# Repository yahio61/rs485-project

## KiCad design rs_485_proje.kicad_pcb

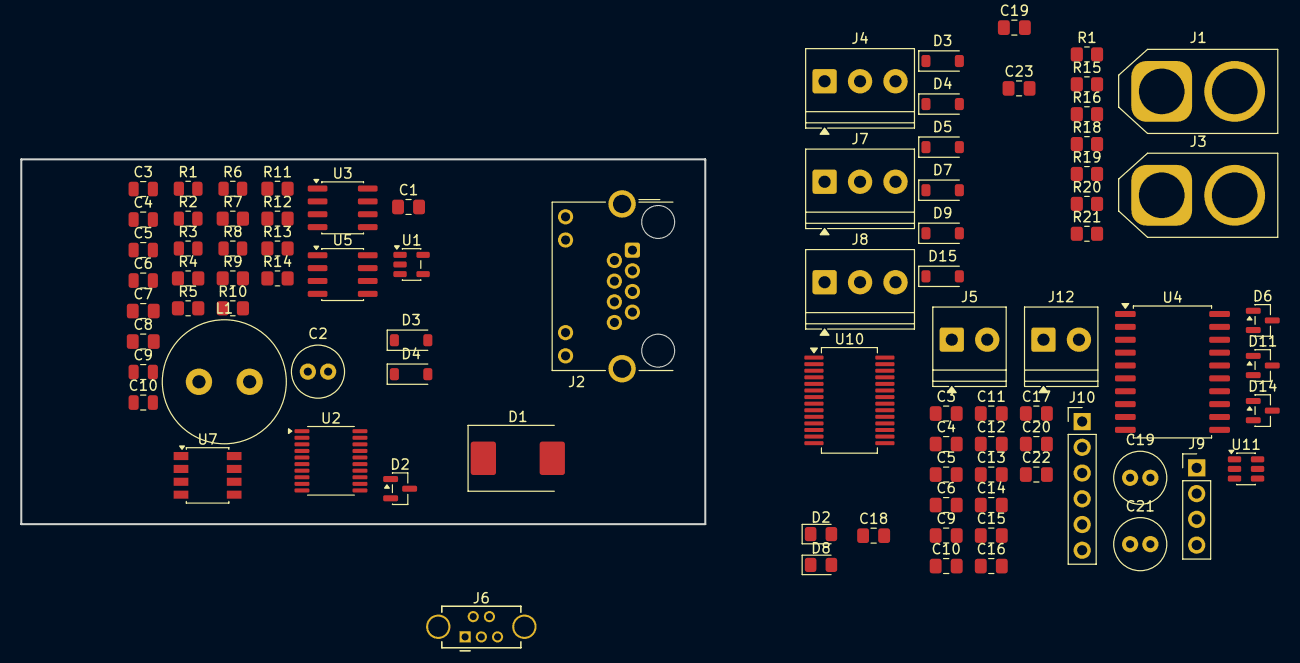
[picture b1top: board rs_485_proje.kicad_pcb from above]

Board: 2 copper layers, 67.5 x 36.0 mm, 86 parts (0 on the bottom side), 52 nets, no tracks yet.

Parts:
C1, C18: 4.7uf; C_0805_2012Metric_Pad1.18x1.45mm_HandSolder
C2: 100uf; C_Radial_D5.0mm_H11.0mm_P2.00mm
C3, C4#2, C5, C6#2: 100nf; C_0805_2012Metric
C3#2, C4, C5#2, C6, C10#2, C11, C12, C13, C14, C16: 100nF; C_0805_2012Metric_Pad1.18x1.45mm_HandSolder
C7: 1uf; C_0805_2012Metric_Pad1.18x1.45mm_HandSolder
C8: 2.2uf; C_0805_2012Metric_Pad1.18x1.45mm_HandSolder
C9, C22: 10nf; C_0805_2012Metric_Pad1.18x1.45mm_HandSolder
C9#2, C10: 4.5n; C_0805_2012Metric
C15: 100nf; C_0805_2012Metric_Pad1.18x1.45mm_HandSolder
C17, C20: 4.7nf; C_0805_2012Metric_Pad1.18x1.45mm_HandSolder
C19, C21: 10uf; C_Radial_D5.0mm_H11.0mm_P2.00mm
C19#2, C23: 10uf; C_0805_2012Metric_Pad1.18x1.45mm_HandSolder
D1: SS34; D_SMC
D2, D8: LED; LED_0805_2012Metric_Pad1.15x1.40mm_HandSolder
D2#2, D6: SM712_SOT23; SOT-23
D3, D4: 3.3V; D_SOD-123
D3#2, D4#2, D5, D7, D9, D15: 1N5819; D_SOD-123
D11, D14: BZX84Cxx; SOT-23
J1: xt60_female; AMASS_XT60-F_1x02_P7.20mm_Vertical
J2: RJ45_LED; RJ45_Connfly_DS1128-09-S8xx-S_Horizontal
J3: xt60_male; AMASS_XT60-M_1x02_P7.20mm_Vertical
J4: Led_conn; TerminalBlock_Phoenix_PT-1,5-3-3.5-H_1x03_P3.50mm_Horizontal
J5: P_E_SENSOR_1; TerminalBlock_Phoenix_PT-1,5-2-3.5-H_1x02_P3.50mm_Horizontal
J6: USB_B_Mini; USB_Mini-B_Tensility_54-00023_Vertical_CircularHoles
J7: H_E_sensor_1; TerminalBlock_Phoenix_PT-1,5-3-3.5-H_1x03_P3.50mm_Horizontal
J8: H_E_sensor_2; TerminalBlock_Phoenix_PT-1,5-3-3.5-H_1x03_P3.50mm_Horizontal
J9: Debug; PinHeader_1x04_P2.54mm_Vertical
J10: Extra_pins; PinHeader_1x06_P2.54mm_Vertical
J12: P_E_SENSOR_2; TerminalBlock_Phoenix_PT-1,5-2-3.5-H_1x02_P3.50mm_Horizontal
L1: 10u; L_Radial_D12.0mm_P5.00mm_Fastron_11P
R1, R18: 1M; R_0805_2012Metric_Pad1.20x1.40mm_HandSolder
R1#2, R2, R6, R8: 1M; R_0805_2012Metric
R3: 120R; R_0805_2012Metric
R4, R10, R13, R14, R21: 10K; R_0805_2012Metric_Pad1.20x1.40mm_HandSolder
R5: 3.24K; R_0805_2012Metric_Pad1.20x1.40mm_HandSolder
R7, R9: 100R; R_0805_2012Metric_Pad1.20x1.40mm_HandSolder
R11, R12: 2.3K; R_0805_2012Metric_Pad1.20x1.40mm_HandSolder
R15, R16, R20: 330R; R_0805_2012Metric_Pad1.20x1.40mm_HandSolder
R19: 120R; R_0805_2012Metric_Pad1.20x1.40mm_HandSolder
U1: AP2112K-3.3; SOT-23-5
U2: STM32G030F6Px; TSSOP-20_4.4x6.5mm_P0.65mm
U3: SN65HVD1781; SOIC-8_3.9x4.9mm_P1.27mm
U4: ADM2587E; SOIC-20W_7.5x12.8mm_P1.27mm
U5: TPS5420D; SOIC-8_3.9x4.9mm_P1.27mm
U7: TLP2161; SSOP-8_3.95x5.21x3.27mm_P1.27mm
U10: FT232RL; SSOP-28_5.3x10.2mm_P0.65mm
U11: USBLC6-2SC6; SOT-23-6

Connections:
+3.3V: C4#2.1, C5.2, C5#2.1, C6.2, C6#2.1, C8.2, C12.1, J9.1, J10.4, R10.1, R13.2, R14.2, R15.2, R16.2, U1.5 (VOUT), U2.4 (VDD), U3.8 (VCC), U10.4 (VCCIO)
+3V3B: C4.1, C9.1, C10#2.1, C19.1, C19#2.1, U4.12 (Visoout), U4.19 (Visoin)
+5V: C15.1, D3#2.1 (K), J7.3, J8.3, R11.1, U7.8 (VCC), U10.20 (VCC)
+24V: C1.1, C18.1, D4#2.1 (K), J2.7, J10.2, U5.7 (VIN)
/Digital_sens_1: R13.1, U2.11 (PA4), U7.7 (VO1)
/Digital_sens_2: R14.1, U2.12 (PA5), U7.6 (VO2)
/LED_Driver: R20.1, U2.17 (PA10/PA12)
/PA_6: J10.6, U2.13 (PA6)
/PA_7: J10.5, U2.14 (PA7)
/Piezzo_sens_1: C9#2.2, C17.2, D4.1 (K), D5.1 (K), D7.1 (K), D14.3 (K), R1.1, R2.2, R8.1, U2.7 (PA0)
/Piezzo_sens_2: C10.2, C20.2, D3.1 (K), D9.1 (K), D11.3 (K), D15.1 (K), R1#2.2, R6.1, R18.1, U2.8 (PA1)
/RS485_A(-): D6.1 (A1), J2.1, R19.1, U4.13 (Y), U4.18 (A)
/RS485_B(+): D6.2 (A2), J2.2, R19.2, U4.15 (Z), U4.17 (B)
/RS_485_D_EN: U2.15 (PA8/PB0/PB1/PB2), U4.6 (DE)
/RS_485_RX_LED: R7.2, U2.2 (PB9/PC14)
/RS_485_R_EN: U2.16 (PA9/PA11), U4.5 (~RE)
/RS_485_TX_LED: R9.2, U2.3 (PC15)
/SWCLK: J9.4, U2.19 (PA14/PA15)
/SWDIO: J9.3, U2.18 (PA13)
/UART_1_RX: U2.1 (PB7/PB8), U4.4 (RxD)
/UART_1_TX: U2.20 (PB3/PB4/PB5/PB6), U4.7 (TxD)
/UART_2_RX: U2.10 (PA3), U10.1 (TXD)
/UART_2_TX: U2.9 (PA2), U10.5 (RXD)
GND: C1.2, C2.2, C4#2.2, C5.1, C5#2.2, C6.1, C6#2.2, C7.1, C8.1, C9#2.1, C10.1, C11.1, C12.2, C13.2, C14.2, C15.2, C16.1, C17.1, C18.2, C20.1, C21.1, C22.1, C23.1, D1.2 (A), D2#2.3 (common), D3.2 (A), D4.2 (A), D7.2 (A), D9.2 (A), D11.1 (A), D14.1 (A), J1.2, J2.8, J2.9, J2.11, J3.2, J4.1, J5.1, J6.5 (GND), J7.1, J8.1, J9.2, J10.1, J12.1, R1.2, R5.2, R6.2, R8.2, R18.2, R21.2, U1.2 (GND), U2.5 (VSS), U3.5 (GND), U4.1 (GND1), U4.3 (GND1), U4.9 (GND1), U4.10 (GND1), U5.6 (GND), U7.2 (C1), U7.3 (C2), U7.5 (GND), U10.7 (GND), U10.18 (GND), U10.21 (GND), U10.25 (AGND), U10.26 (TEST), U11.2 (GND)
GNDB: C4.2, C9.2, C10#2.2, C19.2, C19#2.2, D6.3 (common), J2.3, U4.11 (GND2), U4.14 (GND2), U4.16 (GND2), U4.20 (GND2)
unnamed: C2.1, L1.2
unnamed: C11.2, C16.2, C21.2, C22.2, C23.2, U4.2 (VCC), U4.8 (VCC)
unnamed: C3.1, C3#2.2, D1.1 (K), L1.1, U5.8 (PH)
unnamed: D2#2.1 (A1), R3.1, U3.6 (A)
unnamed: D2#2.2 (A2), R3.2, U3.7 (B)
unnamed: D2.2 (A), R15.1
unnamed: D2.1 (K), U10.22 (CBUS1)
unnamed: C13.1, D3#2.2 (A), J6.1 (VBUS), U11.5 (VBUS)
unnamed: D4#2.2 (A), J1.1, J3.1
unnamed: D5.2 (A), J5.2
unnamed: D8.2 (A), R16.1
unnamed: D8.1 (K), U10.23 (CBUS0)
unnamed: D15.2 (A), J12.2
unnamed: J2.10, R9.1
unnamed: J2.12, R7.1
unnamed: J4.2, R20.2, R21.1
unnamed: J6.3 (D+), U11.1 (I/O1)
unnamed: J6.2 (D-), U11.3 (I/O2)
unnamed: J7.2, R11.2, U7.1 (A1)
unnamed: J8.2, R12.2, U7.4 (A2)
unnamed: C7.2, U1.1 (VIN), U1.3 (EN)
unnamed: R10.2, U2.6 (NRST)
unnamed: C3.2, C3#2.1, U5.1 (BOOT)
unnamed: R4.2, R5.1, U5.4 (VSNS)
unnamed: C14.1, U10.17 (3V3OUT)
unnamed: U10.15 (USBD+), U11.6 (I/O1)
unnamed: U10.16 (USBD-), U11.4 (I/O2)

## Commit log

2026-04-07 ilk commit
2026-04-07 gereksiz dosyalar temizlendi, gitignore devreye sokuldu
2026-04-07 Test commiti
2026-04-07 .history silindi
2026-04-07 telegram eklentisi denemsi
2026-04-07 telegram eklentisi denemsi_2
2026-04-08 yeni brach
2026-04-08 değşiklik
2026-04-08 - Şematik güncellendi. - Malzeme listesi güncellendi.
2026-04-08 deniyorum
2026-04-08 akayaki
2026-04-08 akaykaykay
2026-04-08 hatayi düzelttim
2026-04-12 12.04.2026/11:46
2026-04-12 12.04.2026\15.40
2026-04-26 26.04.2026/10:37
2026-04-26 26/04/12:18
2026-04-26 26/04/12:19
2026-04-26 26/04/12:32
2026-04-26 26/04/14:43
2026-04-26 26/04/18:51
2026-04-26 26/04/18:52
2026-04-27 27/04/15:17
2026-04-27 Şematik neredeyse son haline getirildi. Bazı kozmetik düzeltmeler yapıldı.
2026-05-06 -Şematikte bazı değişimler yapılıd. -İzole Rs-485 entegresine ek kapasitörler eklendi. -Addreslenebilir lede giden 24V'nin sadece harici pil takılıdğında çalışması sağlandı.
2026-05-11 11/05/2026/11:52
2026-05-11 11/05/16:16
2026-05-12 12/05/16:18
2026-05-28 28/05/14:20
2026-06-09 09/06/21:31
2026-06-09 09/06/21:32
2026-06-10 10/06/11:21
2026-06-10 10/06/13:37
